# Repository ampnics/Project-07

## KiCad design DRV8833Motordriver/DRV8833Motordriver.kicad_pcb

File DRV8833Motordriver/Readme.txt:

#kicad Tutorial
*DRV8833Motordriver*

Master kicad with Projects, This is Projects 07.
##schematic

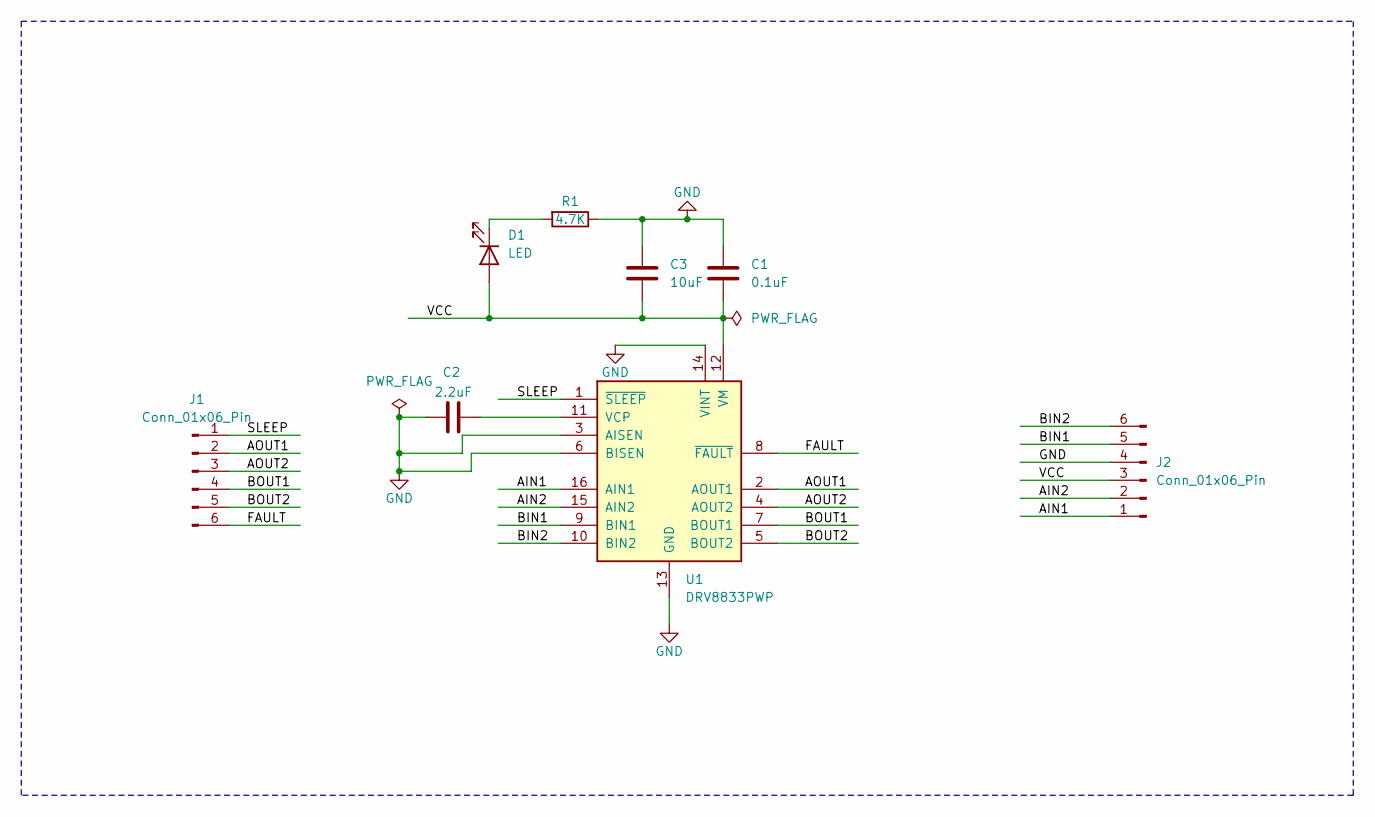
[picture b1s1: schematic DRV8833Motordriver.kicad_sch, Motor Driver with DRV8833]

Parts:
C1: 0.1uF; C_0805_2012Metric
C2: 2.2uF; C_0805_2012Metric
C3: 10uF; CP_EIA-3528-15_AVX-H
D1: LED; LED_0805_2012Metric
J1, J2: Conn_01x06_Pin; PinHeader_1x06_P2.54mm_Vertical
R1: 4.7K; R_0805_2012Metric
U1: DRV8833PWP; HTSSOP-16-1EP_4.4x5mm_P0.65mm_EP3.4x5mm_Mask2.46x2.31mm_The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

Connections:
/AIN1: J2.1, U1.16 (AIN1)
/AIN2: J2.2, U1.15 (AIN2)
/AOUT1: J1.2, U1.2 (AOUT1)
/AOUT2: J1.3, U1.4 (AOUT2)
/BIN1: J2.5, U1.9 (BIN1)
/BIN2: J2.6, U1.10 (BIN2)
/BOUT1: J1.4, U1.7 (BOUT1)
/BOUT2: J1.5, U1.5 (BOUT2)
/FAULT: J1.6, U1.8 (~FAULT)
/SLEEP: J1.1, U1.1 (~SLEEP)
/VCC: C1.2, C3.2, D1.2 (A), J2.3, U1.12 (VM)
GND: C1.1, C2.1, C3.1, J2.4, R1.1, U1.3 (AISEN), U1.6 (BISEN), U1.13 (GND), U1.14 (VINT), U1.17 (GND)
unnamed: D1.1 (K), R1.2
unnamed: C2.2, U1.11 (VCP)

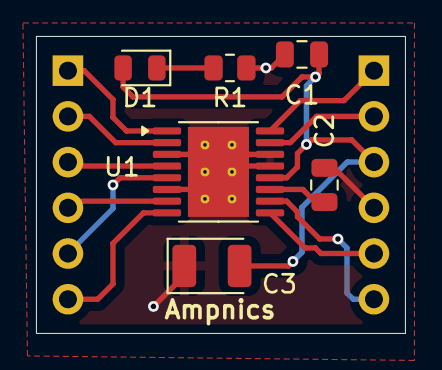
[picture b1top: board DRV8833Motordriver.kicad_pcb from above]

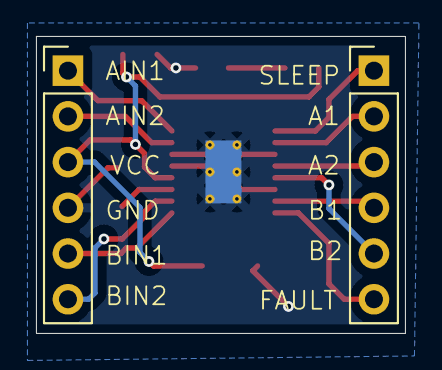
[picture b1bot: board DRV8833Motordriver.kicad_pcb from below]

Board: 2 copper layers, 20.5 x 16.5 mm, 8 parts (2 on the bottom side), 14 nets.
